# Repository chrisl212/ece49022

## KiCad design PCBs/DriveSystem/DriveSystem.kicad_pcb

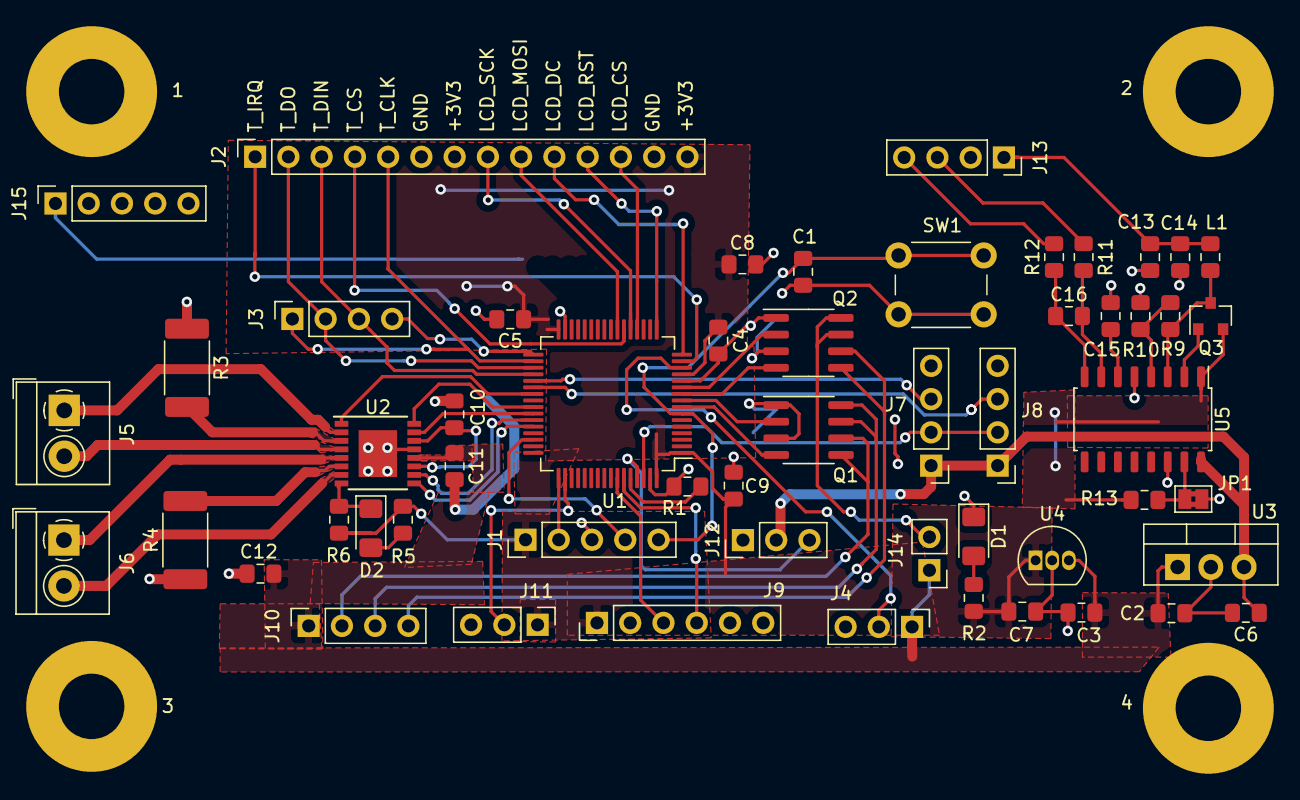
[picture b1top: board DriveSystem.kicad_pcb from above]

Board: 2 copper layers, 59 parts (0 on the bottom side), 65 nets.

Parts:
1, 2, 3, 4: MountingHole_5mm_Pad
C1, C2, C5, C9: 100n; C_0805_2012Metric_Pad1.15x1.40mm_HandSolder
C3: 0.22u; C_0805_2012Metric_Pad1.15x1.40mm_HandSolder
C4, C8: 1u; C_0805_2012Metric_Pad1.15x1.40mm_HandSolder
C6, C12: 0.1u; C_0805_2012Metric_Pad1.15x1.40mm_HandSolder
C7, C11, C14: 10u; C_0805_2012Metric_Pad1.15x1.40mm_HandSolder
C10: 2.2u; C_0805_2012Metric_Pad1.15x1.40mm_HandSolder
C13, C15, C16: .1u; C_0805_2012Metric_Pad1.15x1.40mm_HandSolder
D1, D2: LED; LED_1206_3216Metric_Pad1.42x1.75mm_HandSolder
J1: SWD_Header; PinHeader_1x05_P2.54mm_Vertical
J2: Touchscreen_Header; PinSocket_1x14_P2.54mm_Vertical
J3: SD_Card_Header; PinSocket_1x04_P2.54mm_Vertical
J4: Input_12V; PinHeader_1x03_P2.54mm_Vertical
J5, J6: Screw_Terminal_01x02; TerminalBlock_4Ucon_1x02_P3.50mm_Horizontal
J7: Right_Ultrasonic; PinHeader_1x04_P2.54mm_Vertical
J8: Left_Ultrasonic; PinHeader_1x04_P2.54mm_Vertical
J9: IMU_Header; PinHeader_1x06_P2.54mm_Vertical
J10: Stack_Light; PinSocket_1x04_P2.54mm_Vertical
J11: LPS_Header; PinHeader_1x03_P2.54mm_Vertical
J12: Servo_Header; PinHeader_1x03_P2.54mm_Vertical
J13: Load_Cell_Header; PinSocket_1x04_P2.54mm_Vertical
J14: Conn_01x02_Male; PinHeader_1x02_P2.54mm_Vertical
J15: Conn_01x05_Female; PinSocket_1x05_P2.54mm_Vertical
JP1: SolderJumper_2_Bridged; SolderJumper-2_P1.3mm_Bridged2Bar_Pad1.0x1.5mm
L1: 3.3u; L_0805_2012Metric_Pad1.15x1.40mm_HandSolder
Q1, Q2: FDS6898A; SOIC-8_3.9x4.9mm_P1.27mm
Q3: MMBT3906; SOT-23
R1, R2, R5: 510; R_0805_2012Metric_Pad1.15x1.40mm_HandSolder
R3, R4: 0.25; R_2512_6332Metric_Pad1.52x3.35mm_HandSolder
R6: 3.3k; R_0805_2012Metric_Pad1.15x1.40mm_HandSolder
R9: 20k; R_0805_2012Metric_Pad1.15x1.40mm_HandSolder
R10: 8.2k; R_0805_2012Metric_Pad1.15x1.40mm_HandSolder
R11, R12: 100; R_0805_2012Metric_Pad1.15x1.40mm_HandSolder
R13: 10k; R_0805_2012Metric_Pad1.15x1.40mm_HandSolder
SW1: SW_Push; SW_PUSH_6mm
U1: STM32F051R8Tx; LQFP-64_10x10mm_P0.5mm
U2: DRV8848; TSSOP-16-1EP_4.4x5mm_P0.65mm
U3: LM7805_TO220; TO-220-3_Vertical
U4: LM2936-3.3_TO92; TO-92_Inline
U5: HX711; SOP-16_4.55x10.3mm_P1.27mm

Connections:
+3V3: C4.1, C5.1, C7.1, C8.1, C9.1, J1.1, J2.7, J2.14, J9.1, J11.1, Q3.2, R2.1, R5.1, R6.1, R13.1, U1.1, U1.13, U1.32, U1.64, U4.1, U5.1
+5V: C6.1, J7.1, J8.1, J12.2, U3.3, U5.16
+12V: C2.1, C3.1, C11.1, C12.1, J4.1, J10.1, J14.1, U2.12, U3.1, U4.3
/AIN1: U1.41, U2.16
/AIN2: U1.42, U2.15
/BATLVL: J4.2, U1.14
/BIN1: U1.44, U2.9
/BIN2: U1.43, U2.10
/BOOT0: R1.1, U1.60
/Buzz: J14.2, Q2.7, Q2.8
/Buzzer: Q2.2, U1.11
/ECHOl: J8.3, U1.38
/ECHOr: J7.3, U1.37
/IMU_SCL: J9.3, U1.58
/IMU_SDA: J9.4, U1.59
/LCD_CS: J2.12, U1.20
/LCD_DC: J2.10, U1.16
/LCD_RESET: J2.11, U1.17
/LCD_SCK: J2.8, U1.21
/LCD_SDI_MOSI: J2.9, U1.23
/LC_AVDD: C13.2, C14.2, J13.1, L1.1
/LC_INA+: J13.4, R12.2
/LC_INA-: J13.3, R11.2
/LPS_SRL: J11.2, U1.50
/NRST: C1.1, J1.5, SW1.1, U1.7
/PB0: J15.5, U1.26
/PB1: J15.4, U1.27
/PB2: J15.3, U1.28
/PB10: J15.2, U1.29
/PB11: J15.1, U1.30
/SD_CS: J3.4, U1.33
/SV_FB: J12.3, U1.61
/SWCLK: J1.2, U1.49
/SWDIO: J1.4, U1.46
/TRIG: J7.2, J8.2, U1.62
/T_CLK: J2.5, J3.1, U1.34
/T_CS: J2.4, U1.22
/T_DIN: J2.3, J3.3, U1.36
/T_DO: J2.2, J3.2, U1.35
/T_IRQ: J2.1, U1.15
/VINT: C10.1, U2.11, U2.14
/nFAULT: D2.1, R6.2, U2.8
/nSLEEP: U1.39, U2.1
/sGreen: Q1.4, U1.8
/sGreeni: J10.2, Q1.5, Q1.6
/sRed: Q2.4, U1.10
/sRedi: J10.4, Q2.5, Q2.6
/sYellow: Q1.2, U1.9
/sYellowi: J10.3, Q1.7, Q1.8
GND: C1.2, C2.2, C3.2, C4.2, C5.2, C6.2, C7.2, C8.2, C9.2, C10.2, C11.2, C12.2, C13.1, C14.1, C15.2, D1.1, J1.3, J2.6, J2.13, J4.3, J7.4, J8.4, J9.2, J9.5, J9.6, J11.3, J12.1, J13.2, JP1.2, Q1.1, Q1.3, Q2.1, Q2.3, R1.2, R3.1, R4.1, R10.2, SW1.2, U1.12, U1.31, U1.63, U2.13, U2.17, U3.2, U4.2, U5.5, U5.14
unnamed: C15.1, U5.6
unnamed: C16.1, R12.1, U5.8
unnamed: C16.2, R11.1, U5.7
unnamed: D1.2, R2.2
unnamed: D2.2, R5.2
unnamed: J5.1, U2.2
unnamed: J5.2, U2.4
unnamed: J6.1, U2.5
unnamed: J6.2, U2.7
unnamed: JP1.1, R13.2, U5.15
unnamed: L1.2, Q3.3, R9.1, U5.3
unnamed: Q3.1, U5.2
unnamed: R3.2, U2.3
unnamed: R4.2, U2.6
unnamed: R9.2, R10.1, U5.4

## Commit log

2019-08-26 initial
2019-09-04 robo
2019-09-05 encoder works
2019-09-05 starting FAT32/SD
2019-09-06 progress
2019-09-12 sd working
2019-09-13 fat almost done
2019-09-13 touch
2019-09-17 preview
2019-09-20 make
2019-09-26 initial commit for drive system
2019-09-26 test
2019-09-26 Added .o files
2019-09-26 Added channels for B input
2019-10-01 test commit
2019-10-01 Speed and Heading PID implemented
2019-10-10 prog
2019-10-10 Added demo code, made structs work for PID
2019-10-15 demo
2019-10-16 added pcb folder
2019-10-16 added ultrasonic sensors
2019-10-16 Added microcontroller support
2019-10-16 Added circuit descriptions
2019-10-17 added touchscreen and stack light stuff
2019-10-18 Added labels and notes
2019-10-19 Added part footprints
2019-10-19 added load cell and regulator
2019-10-19 Started pcb tracing
2019-10-21 First pcb thing done (gotta redo a lot of it)
2019-10-23 Pcb almost done
    :
2019-10-23 modfied pcb
2019-10-24 Create LoadCellSch
2019-11-14 refactor
2019-12-03 partially working
2019-12-06 done
